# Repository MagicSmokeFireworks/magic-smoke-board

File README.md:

# magic-smoke-board
Electronics schematics, layouts, and part info for the awesome Magic Smoke board.

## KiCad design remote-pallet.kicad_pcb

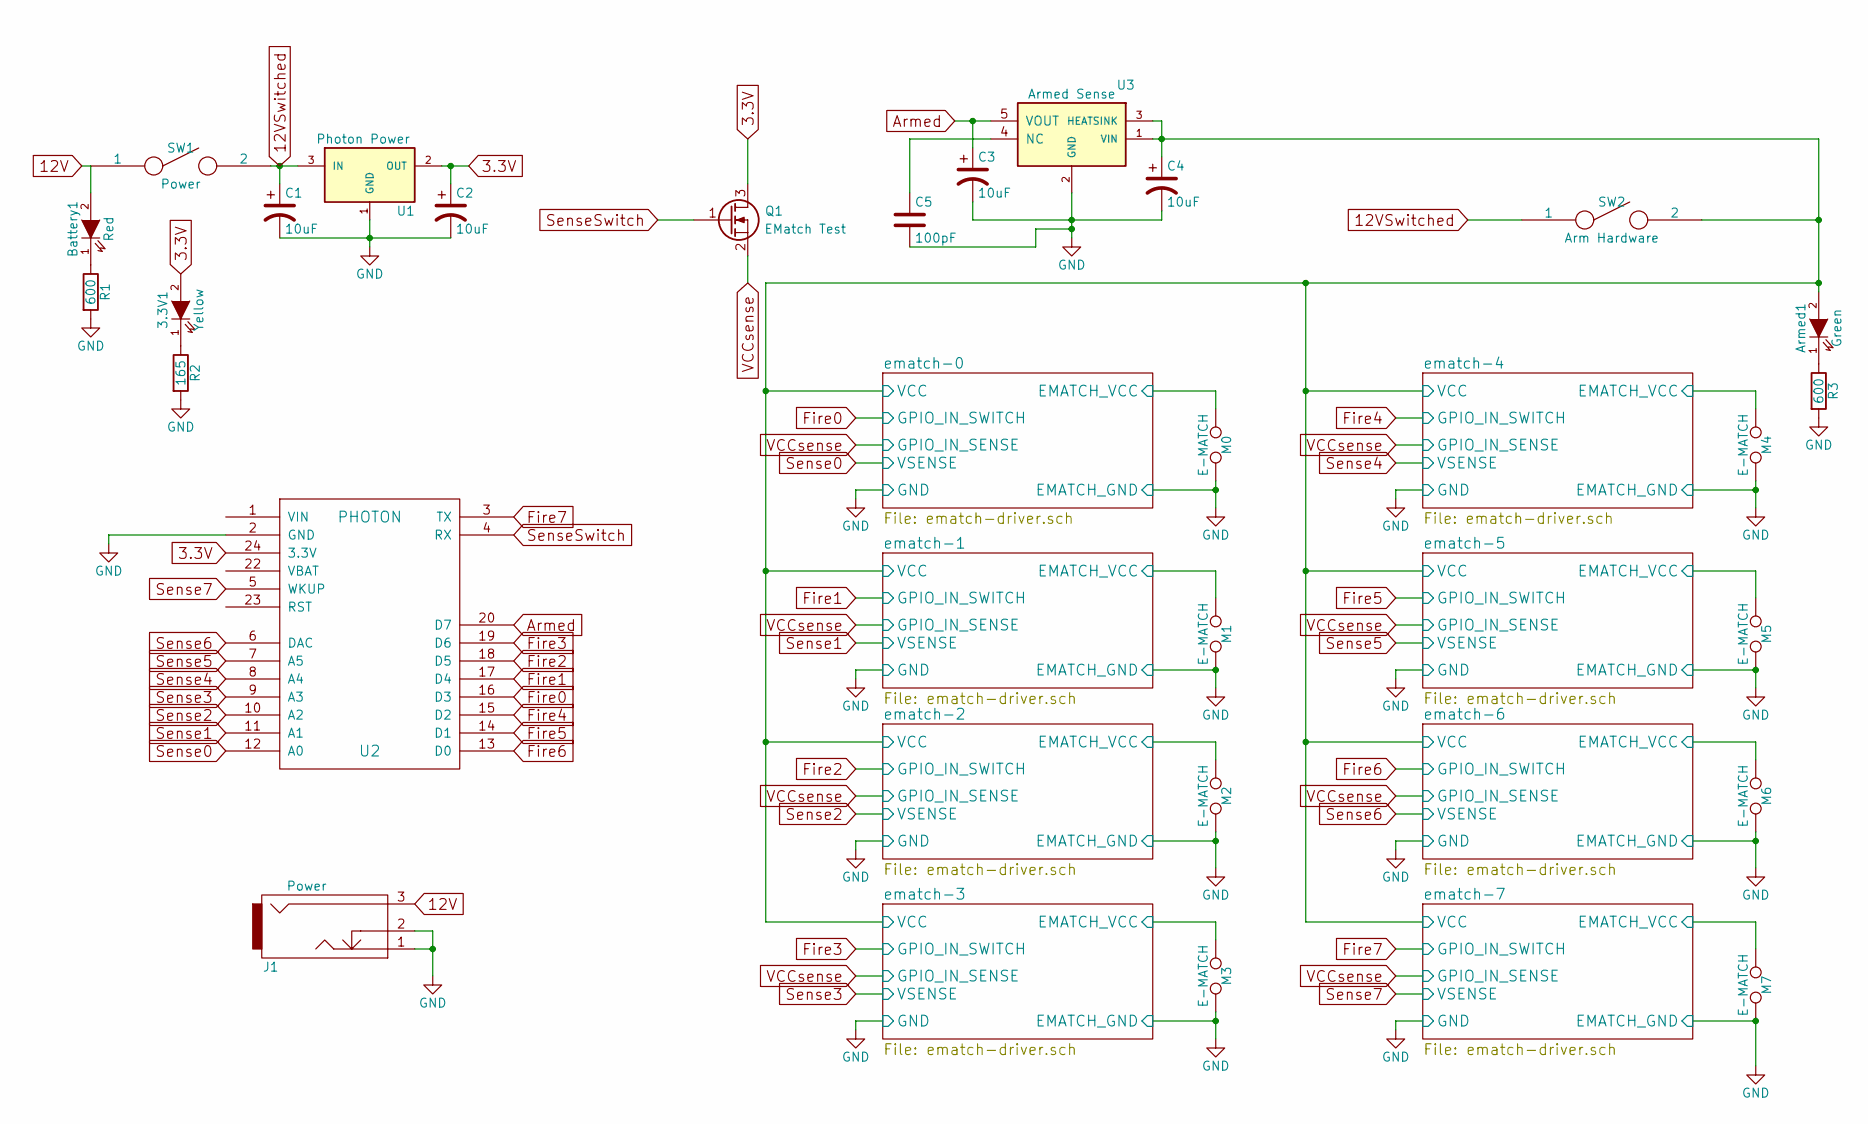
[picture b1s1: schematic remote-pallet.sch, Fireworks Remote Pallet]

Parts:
3.3V1: Yellow; LED_0603; digikey part no 732-4981-1-ND
Armed1: Green; LED_0603; digikey part no 732-4971-1-ND
Battery1: Red; LED_0603; digikey part no 732-4978-1-ND
C1, C2: 10uF; C_0805_HandSoldering; digikey part no 511-1683-1-ND
C3: 10uF; C_0805_HandSoldering; digikey part no 587-1290-1-ND
C4: 10uF; C_0805_HandSoldering; digikey part no 490-5523-1-ND
C5: 100pF; C_0805_HandSoldering
J1: Power; PJ-082BH-Barrel-Connector; digikey part no CP-082BHCT-ND
M0, M1, M2, M3, M4, M5, M6, M7: E-MATCH; TerminalBlock_Altech_AK300-2_P5.00mm; digikey part no 277-2518-ND
Q1: EMatch Test; SOT-23_Handsoldering; digikey part no SSM3K324RLFCT-ND
R1, R3: 600; R_0603_HandSoldering; digikey part no 311-600HCT-ND
R2: 165; R_0603_HandSoldering; digikey part no 311-165HRCT-ND
SW1: Power; M2011LL1W01; digikey part no 360-3287-ND
SW2: Arm Hardware; M2011LL1W01; digikey part no 360-3287-ND
U1: Photon Power; TO-263-3Lead; digikey part no LM1085ISX-3.3/NOPBCT-ND
U2: PHOTON
U3: Armed Sense; SOT-23-5; digikey part no AP2202K-3.3TRG1DICT-ND

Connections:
3.3V: 3.3V1.2 (A), C2.1, Q1.3 (D), U1.2 (OUT), U2.24 (3.3V)
12V: Battery1.2 (A), J1.3, SW1.1
12VSwitched: C1.1, SW1.2, SW2.1, U1.3 (IN)
/ematch-0/EMATCH_VCC: M0.1; also elsewhere on the board
/ematch-0/VCC: Armed1.2 (A), C4.1, SW2.2, U3.1 (VIN), U3.3 (HEATSINK); also elsewhere on the board
/ematch-1/EMATCH_VCC: M1.1; also elsewhere on the board
/ematch-2/EMATCH_VCC: M2.1; also elsewhere on the board
/ematch-3/EMATCH_VCC: M3.1; also elsewhere on the board
/ematch-4/EMATCH_VCC: M4.1; also elsewhere on the board
/ematch-5/EMATCH_VCC: M5.1; also elsewhere on the board
/ematch-6/EMATCH_VCC: M6.1; also elsewhere on the board
/ematch-7/EMATCH_VCC: M7.1; also elsewhere on the board
Armed: C3.1, U2.20 (D7), U3.5 (VOUT)
Fire0: U2.16 (D3); also elsewhere on the board
Fire1: U2.17 (D4); also elsewhere on the board
Fire2: U2.18 (D5); also elsewhere on the board
Fire3: U2.19 (D6); also elsewhere on the board
Fire4: U2.15 (D2); also elsewhere on the board
Fire5: U2.14 (D1); also elsewhere on the board
Fire6: U2.13 (D0); also elsewhere on the board
Fire7: U2.3 (TX); also elsewhere on the board
GND: C1.2, C2.2, C3.2, C4.2, C5.2, J1.1, J1.2, M0.2, M1.2, M2.2, M3.2, M4.2, M5.2, M6.2, M7.2, R1.2, R2.2, R3.2, U1.1 (GND), U2.2 (GND), U3.2 (GND); also elsewhere on the board
unnamed: 3.3V1.1 (K), R2.1
unnamed: Armed1.1 (K), R3.1
unnamed: Battery1.1 (K), R1.1
unnamed: C5.1, U3.4 (NC)
Sense0: U2.12 (A0); also elsewhere on the board
Sense1: U2.11 (A1); also elsewhere on the board
Sense2: U2.10 (A2); also elsewhere on the board
Sense3: U2.9 (A3); also elsewhere on the board
Sense4: U2.8 (A4); also elsewhere on the board
Sense5: U2.7 (A5); also elsewhere on the board
Sense6: U2.6 (DAC); also elsewhere on the board
Sense7: U2.5 (WKUP); also elsewhere on the board
SenseSwitch: Q1.1 (G), U2.4 (RX)
VCCsense: Q1.2 (S); also elsewhere on the board

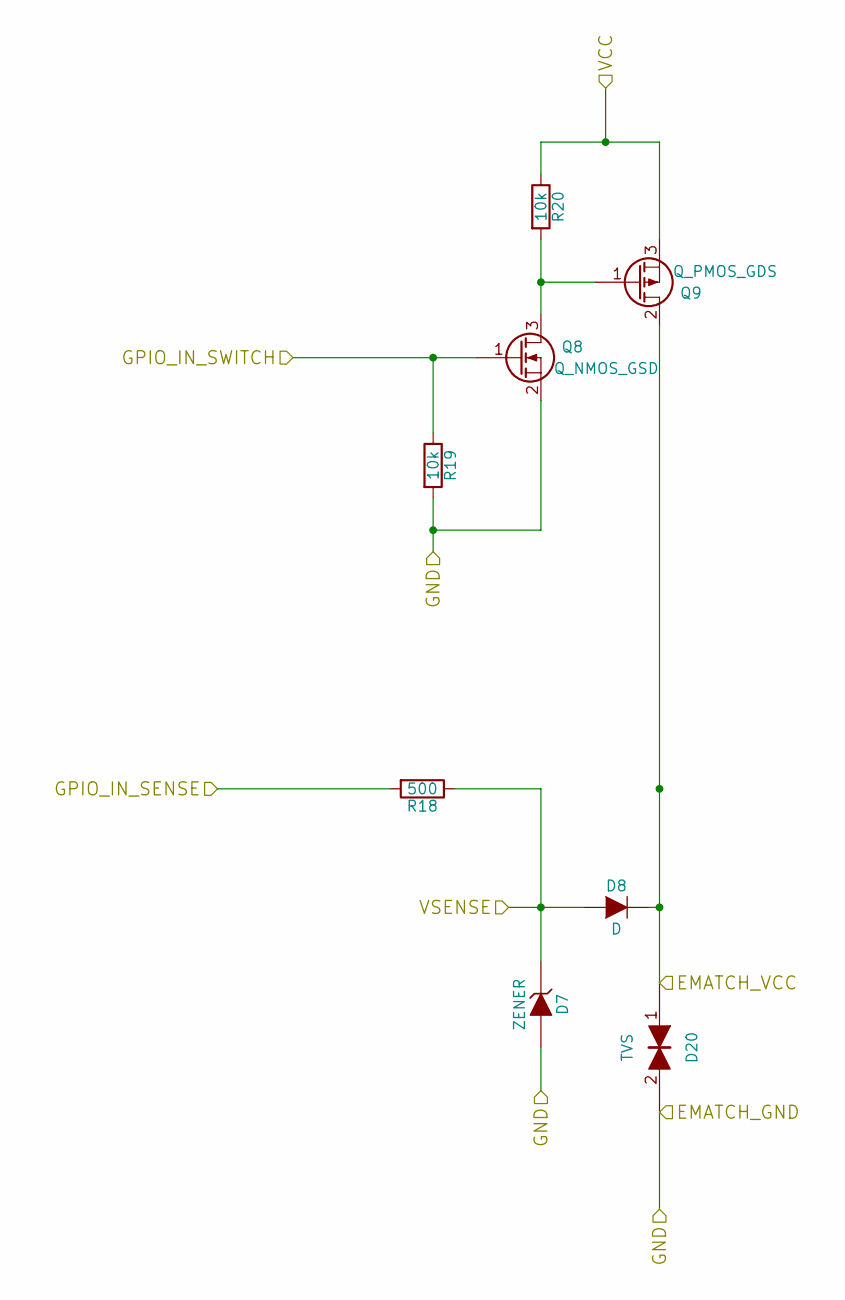
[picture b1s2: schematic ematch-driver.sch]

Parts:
D1: ZENER; SOD-123; digikey part no CD0603-Z3V3CT-ND
D2: D; SOD-123; digikey part no 641-1282-2-ND
D17: TVS; D_SMA_Handsoldering; digikey part no SMAJ30CALFTR-ND
Q2: Q_NMOS_GSD; SOT-23_Handsoldering; digikey part no SSM3K324RLFCT-ND
Q3: Q_PMOS_GDS; TO-252-2Lead; digikey part no NTD2955T4GOSCT-ND
R9: 500; R_0603_HandSoldering; digikey part no 311-499HRCT-ND
R10, R11: 10k; R_0603_HandSoldering; digikey part no 311-10KGRCT-ND

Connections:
/ematch-0/EMATCH_VCC: D2.1 (K), D17.1, Q3.2 (D); also elsewhere on the board
/ematch-0/VCC: Q3.3 (S), R11.1; also elsewhere on the board
Fire0: Q2.1 (G), R10.1; also elsewhere on the board
GND: D1.2 (A), D17.2, Q2.2 (S), R10.2; also elsewhere on the board
unnamed: Q2.3 (D), Q3.1 (G), R11.2
Sense0: D1.1 (K), D2.2 (A), R9.1; also elsewhere on the board
VCCsense: R9.2; also elsewhere on the board

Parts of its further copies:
D3, D5, D7, D9, D11, D13, D15: ZENER; SOD-123; digikey part no CD0603-Z3V3CT-ND
D4, D6, D8, D10, D12, D14, D16: D; SOD-123; digikey part no 641-1282-2-ND
D18, D19, D20, D21, D22, D23, D24: TVS; D_SMA_Handsoldering; digikey part no SMAJ30CALFTR-ND
Q4, Q6, Q8, Q10, Q12, Q14, Q16: Q_NMOS_GSD; SOT-23_Handsoldering; digikey part no SSM3K324RLFCT-ND
Q5, Q7, Q9, Q11, Q13, Q15, Q17: Q_PMOS_GDS; TO-252-2Lead; digikey part no NTD2955T4GOSCT-ND
R12, R15, R18, R21, R24, R27, R30: 500; R_0603_HandSoldering; digikey part no 311-499HRCT-ND
R13, R14, R16, R17, R19, R20, R22, R23, R25, R26, R28, R29, R31, R32: 10k; R_0603_HandSoldering; digikey part no 311-10KGRCT-ND

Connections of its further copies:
/ematch-0/VCC: Q5.3 (S), Q7.3 (S), Q9.3 (S), Q11.3 (S), Q13.3 (S), Q15.3 (S), Q17.3 (S), R14.1, R17.1, R20.1, R23.1, R26.1, R29.1, R32.1; also elsewhere on the board
/ematch-1/EMATCH_VCC: D4.1 (K), D18.1, Q5.2 (D); also elsewhere on the board
/ematch-2/EMATCH_VCC: D6.1 (K), D19.1, Q7.2 (D); also elsewhere on the board
/ematch-3/EMATCH_VCC: D8.1 (K), D20.1, Q9.2 (D); also elsewhere on the board
/ematch-4/EMATCH_VCC: D10.1 (K), D21.1, Q11.2 (D); also elsewhere on the board
/ematch-5/EMATCH_VCC: D12.1 (K), D22.1, Q13.2 (D); also elsewhere on the board
/ematch-6/EMATCH_VCC: D14.1 (K), D23.1, Q15.2 (D); also elsewhere on the board
/ematch-7/EMATCH_VCC: D16.1 (K), D24.1, Q17.2 (D); also elsewhere on the board
Fire1: Q4.1 (G), R13.1; also elsewhere on the board
Fire2: Q6.1 (G), R16.1; also elsewhere on the board
Fire3: Q8.1 (G), R19.1; also elsewhere on the board
Fire4: Q10.1 (G), R22.1; also elsewhere on the board
Fire5: Q12.1 (G), R25.1; also elsewhere on the board
Fire6: Q14.1 (G), R28.1; also elsewhere on the board
Fire7: Q16.1 (G), R31.1; also elsewhere on the board
GND: D3.2 (A), D5.2 (A), D7.2 (A), D9.2 (A), D11.2 (A), D13.2 (A), D15.2 (A), D18.2, D19.2, D20.2, D21.2, D22.2, D23.2, D24.2, Q4.2 (S), Q6.2 (S), Q8.2 (S), Q10.2 (S), Q12.2 (S), Q14.2 (S), Q16.2 (S), R13.2, R16.2, R19.2, R22.2, R25.2, R28.2, R31.2; also elsewhere on the board
unnamed: Q4.3 (D), Q5.1 (G), R14.2
unnamed: Q6.3 (D), Q7.1 (G), R17.2
unnamed: Q8.3 (D), Q9.1 (G), R20.2
unnamed: Q10.3 (D), Q11.1 (G), R23.2
unnamed: Q12.3 (D), Q13.1 (G), R26.2
unnamed: Q14.3 (D), Q15.1 (G), R29.2
unnamed: Q16.3 (D), Q17.1 (G), R32.2
Sense1: D3.1 (K), D4.2 (A), R12.1; also elsewhere on the board
Sense2: D5.1 (K), D6.2 (A), R15.1; also elsewhere on the board
Sense3: D7.1 (K), D8.2 (A), R18.1; also elsewhere on the board
Sense4: D9.1 (K), D10.2 (A), R21.1; also elsewhere on the board
Sense5: D11.1 (K), D12.2 (A), R24.1; also elsewhere on the board
Sense6: D13.1 (K), D14.2 (A), R27.1; also elsewhere on the board
Sense7: D15.1 (K), D16.2 (A), R30.1; also elsewhere on the board
VCCsense: R12.2, R15.2, R18.2, R21.2, R24.2, R27.2, R30.2; also elsewhere on the board

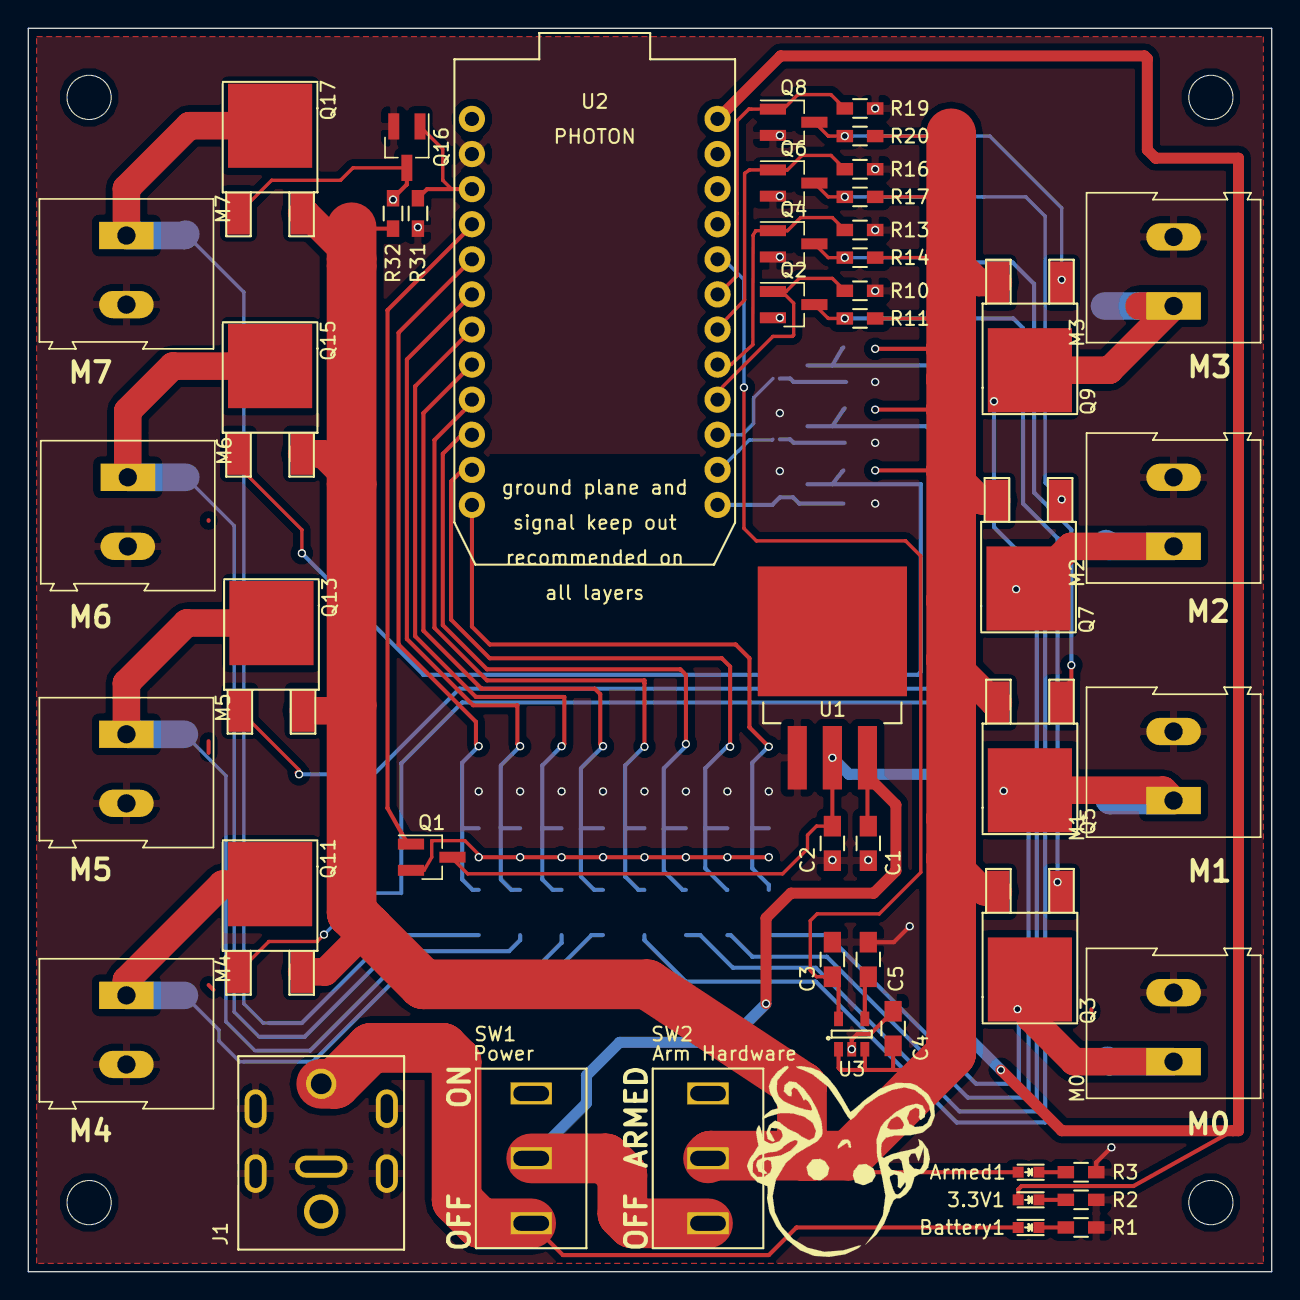
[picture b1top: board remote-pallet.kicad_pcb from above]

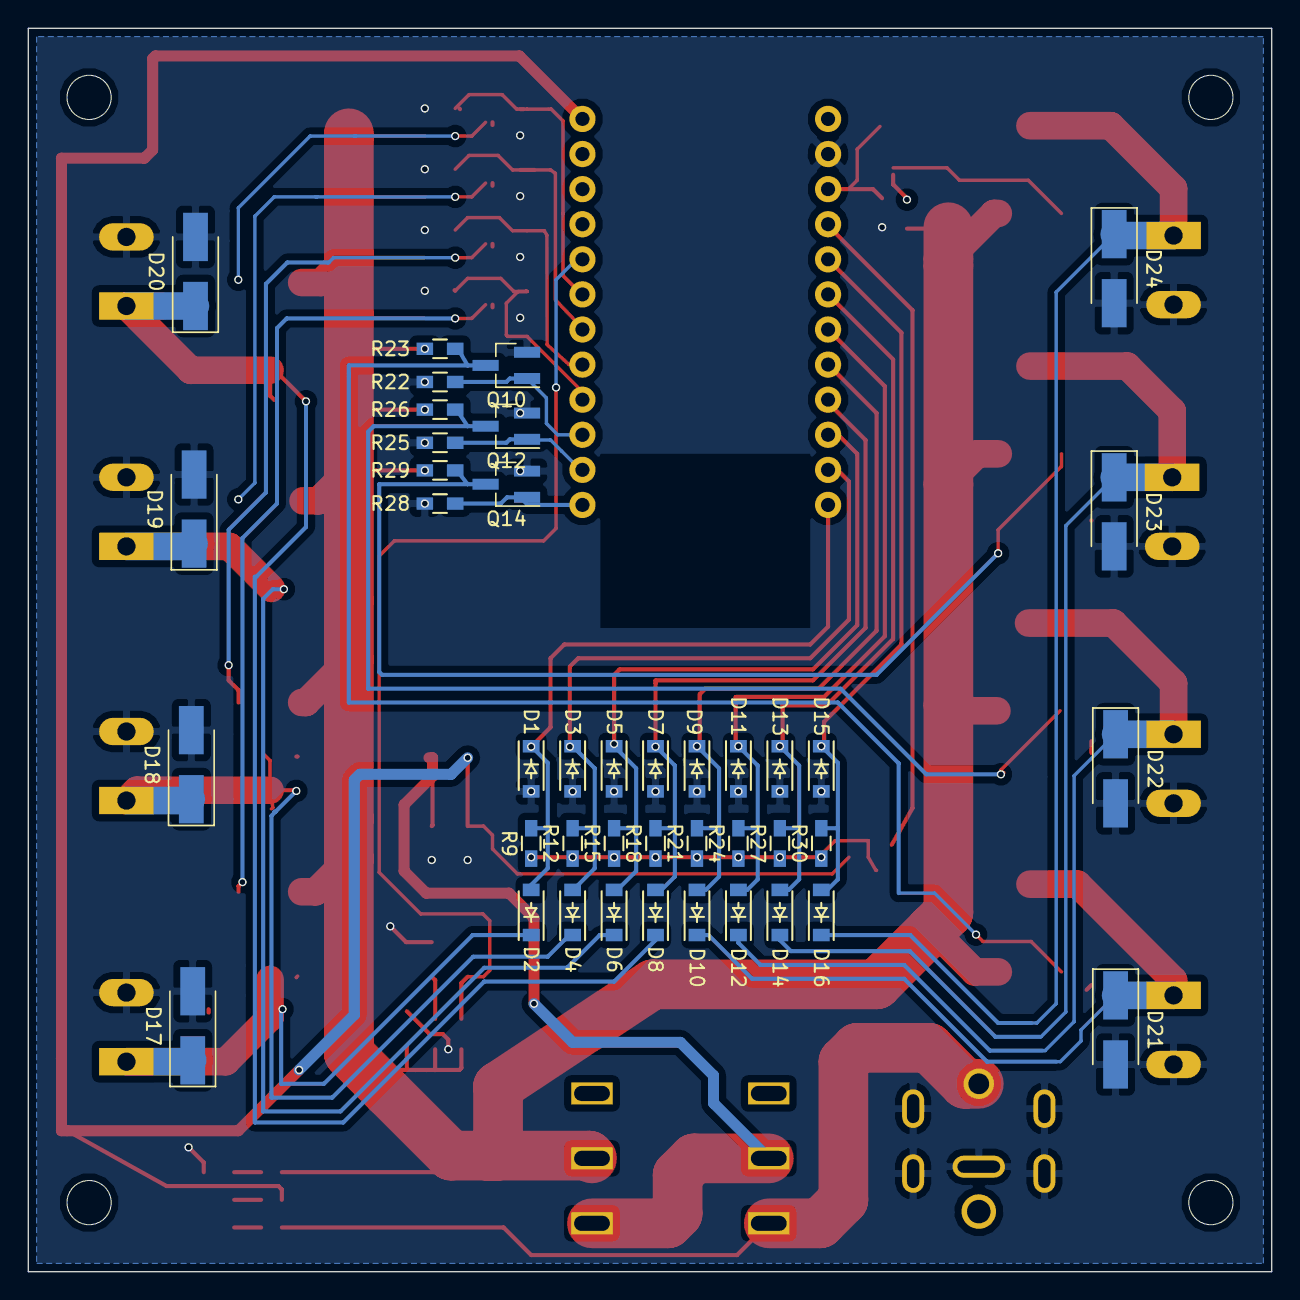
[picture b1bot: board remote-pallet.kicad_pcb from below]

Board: 2 copper layers, 90.0 x 90.0 mm, 90 parts (41 on the bottom side), 44 nets.

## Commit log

2016-06-15 adding hardware
2017-02-12 fucking mac windows manager is a pile of shit
2019-06-02 Updates from 2018 rev
